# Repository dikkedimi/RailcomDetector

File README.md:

# RailcomDetector
 based on https://www.rmweb.co.uk/community/index.php?/topic/123719-handmade-railcom/
 see railcom specification document at http://normen.railcommunity.de/RCN-217.pdf

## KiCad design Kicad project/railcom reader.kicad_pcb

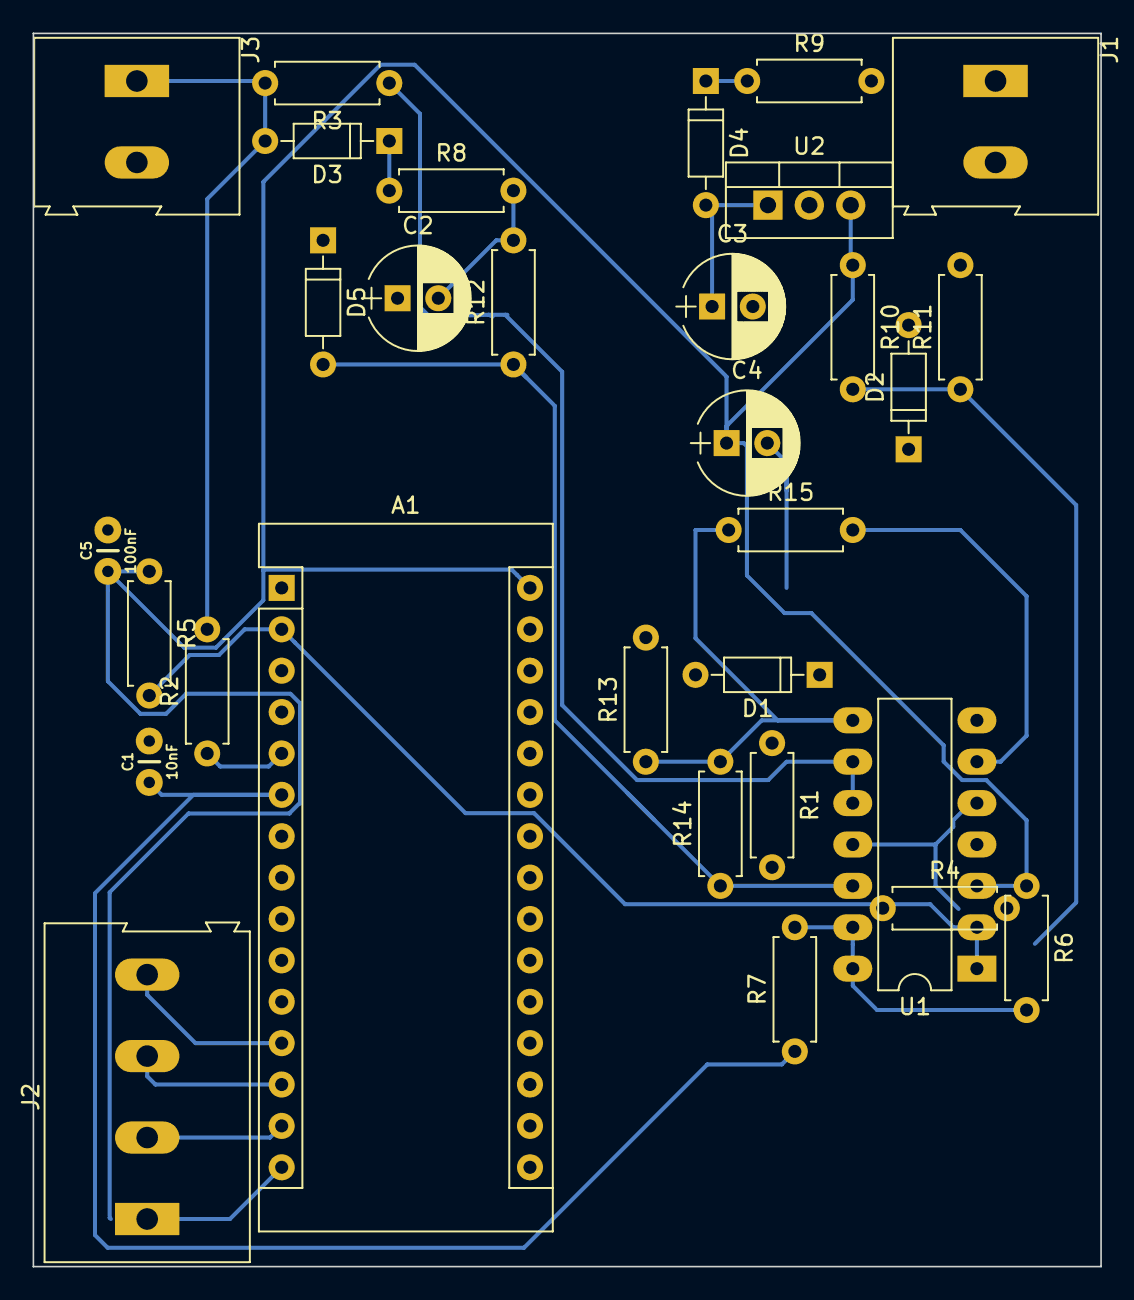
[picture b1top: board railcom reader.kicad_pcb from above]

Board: 2 copper layers, 65.5 x 75.7 mm, 31 parts (0 on the bottom side), 20 nets.

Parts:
A1: Arduino_Nano_v3.x; Arduino_Nano
C1: 10nF; CAP-PTH-2.54
C2, C4: 100µF; CP_Radial_D6.3mm_P2.50mm
C3: 220µF; CP_Radial_D6.3mm_P2.50mm
C5: 100nF; CAP-PTH-2.54
D1, D2: D_Schottky_Small; D_DO-35_SOD27_P7.62mm_Horizontal
D3, D4, D5: DIODE; D_DO-35_SOD27_P7.62mm_Horizontal
J1: BOOSTER_IN; TerminalBlock_Altech_AK300-2_P5.00mm
J2: Signal output 1; TerminalBlock_Altech_AK300-4_P5.00mm
J3: TRACK_OUT; TerminalBlock_Altech_AK300-2_P5.00mm
R1: 1,8; R_Axial_DIN0207_L6.3mm_D2.5mm_P7.62mm_Horizontal
R2, R3: 47K; R_Axial_DIN0207_L6.3mm_D2.5mm_P7.62mm_Horizontal
R4, R5, R7, R11: 1K; R_Axial_DIN0207_L6.3mm_D2.5mm_P7.62mm_Horizontal
R6: 2.2K; R_Axial_DIN0207_L6.3mm_D2.5mm_P7.62mm_Horizontal
R8, R12: 220; R_Axial_DIN0207_L6.3mm_D2.5mm_P7.62mm_Horizontal
R9: 33; R_Axial_DIN0207_L6.3mm_D2.5mm_P7.62mm_Horizontal
R10: 270K; R_Axial_DIN0207_L6.3mm_D2.5mm_P7.62mm_Horizontal
R13: 820; R_Axial_DIN0207_L6.3mm_D2.5mm_P7.62mm_Horizontal
R14: 33K; R_Axial_DIN0207_L6.3mm_D2.5mm_P7.62mm_Horizontal
R15: 0; R_Axial_DIN0207_L6.3mm_D2.5mm_P7.62mm_Horizontal
U1: LM339; DIP-14_W7.62mm_LongPads
U2: L7805; TO-220-3_Vertical

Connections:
/+5V: A1.30, C4.1, C5.1, R5.1, R6.1, R10.1, U1.3, U2.3
/+18mV: R10.2, R11.1, U1.5, U1.11
/-18mV: R13.1, R14.2, R15.1, R15.2, U1.6, U1.8
/BOOSTER_IN_A: J1.1, R9.2
/DCC: D3.2, J3.1, R2.2, R3.2
/DCC_IN: A1.5, R2.1
/RAILCOM_IN: A1.2, R5.2, U1.1, U1.2
/VCC: D5.2, R12.1, R14.1, U1.12
/WINDOW_DETECT: A1.6, C1.1, R7.1
GND: A1.4, A1.29, C1.2, C2.1, C3.2, C4.2, C5.2, D1.1, D1.2, D2.1, D2.2, D5.1, J1.2, J3.2, R1.1, R1.2, R4.1, R11.2, R13.2, U1.4, U1.7, U2.2
unnamed: A1.12, J2.4
unnamed: A1.13, J2.3
unnamed: A1.14, J2.2
unnamed: A1.15, J2.1
unnamed: C2.2, R8.2, R12.2
unnamed: C3.1, D4.2, U2.1
unnamed: D3.1, R8.1
unnamed: D4.1, R9.1
unnamed: R3.1, R4.2, U1.9, U1.10
unnamed: R6.2, R7.2, U1.13, U1.14

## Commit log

2020-03-26 First commit
    first schematic put into kicad. Although I'm not sure I've interpeted the DCC trac connection properly. I'm weary of connecting an AC signal directly to ground...
2020-03-26 update schematic, netlist, pcb concept
    modifications in comparing to railcom specification docs
    original "splice" graphic found in topic was a bit confusing (imho)
2020-04-13 updated net labels & corrected some mistakes.
    still getting 10 volts on the 7805. why though?
2020-04-30 included some reference docs
    The schematic is not my own design, it is based on the design found on RMWeb
    https://www.rmweb.co.uk/community/index.php?/topic/123719-handmade-railcom/
2020-06-17 added my railcom sniffer sketch
    So yall can check whether I'm doing this right xD
